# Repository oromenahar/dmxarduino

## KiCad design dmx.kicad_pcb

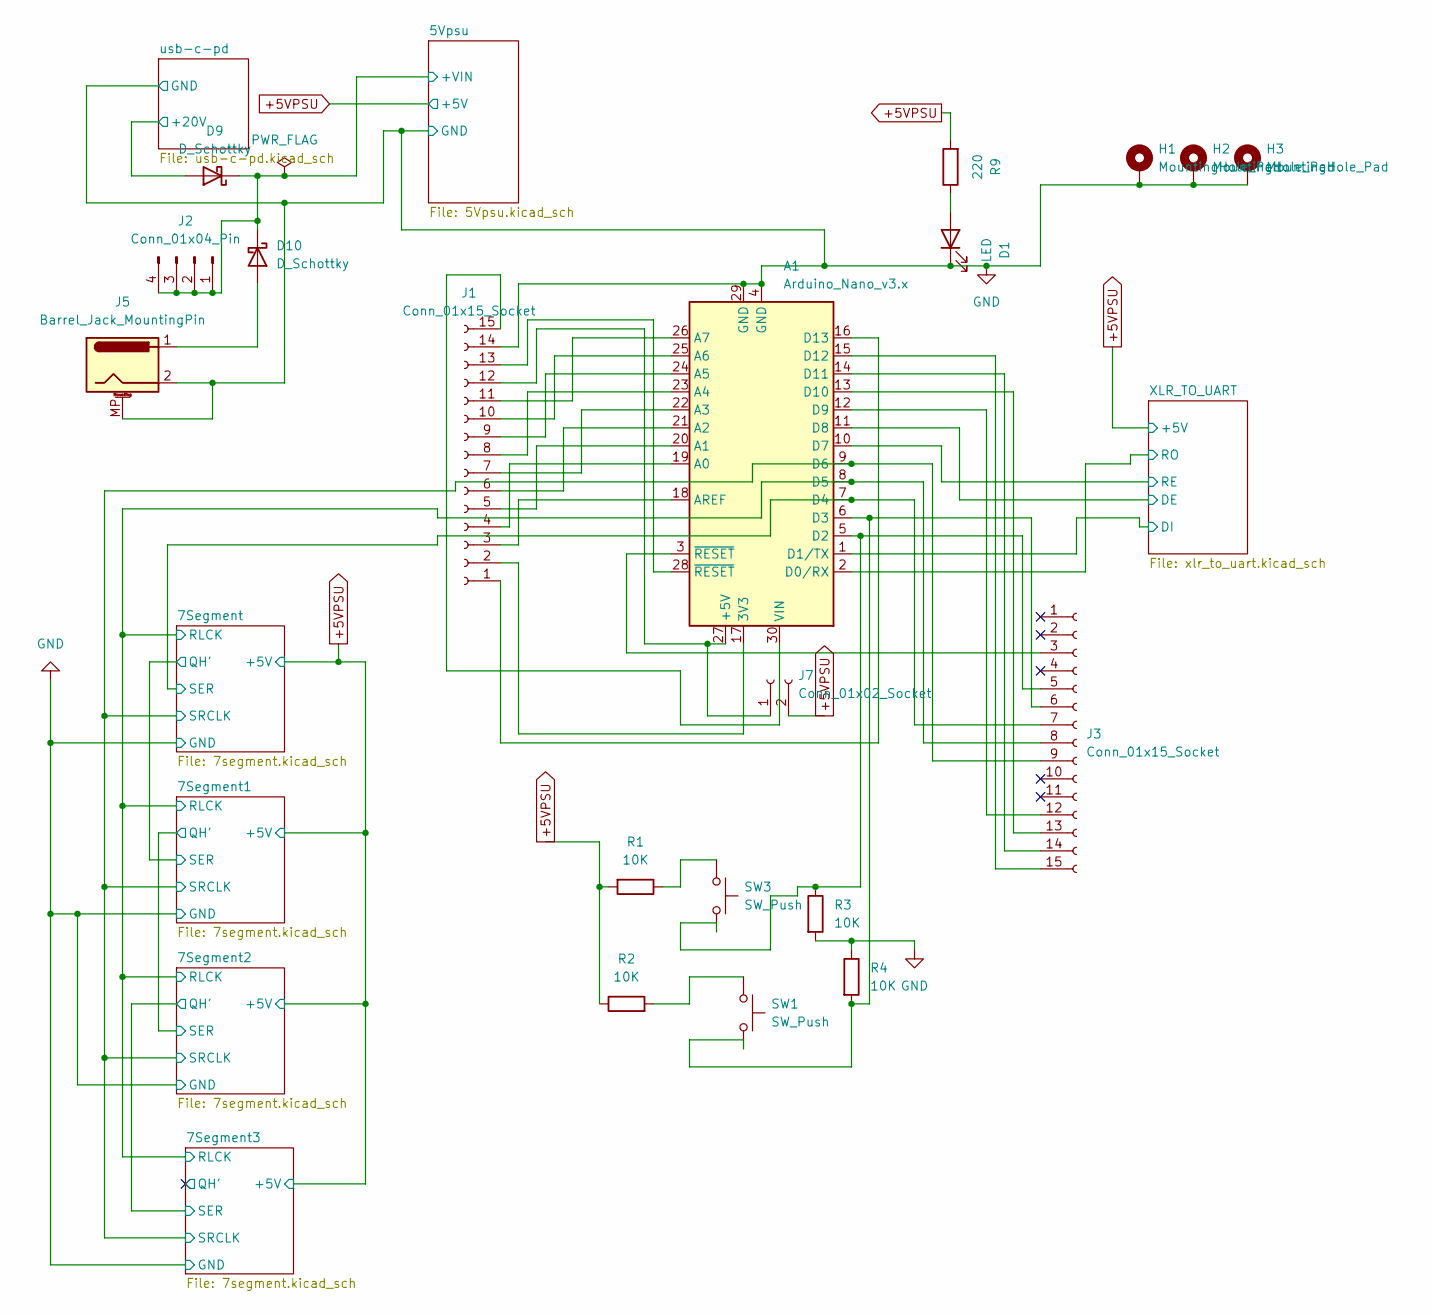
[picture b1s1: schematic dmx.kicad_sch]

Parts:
A1: Arduino_Nano_v3.x; Arduino_Nano_WithMountingHoles
D1: LED; LED_0603_1608Metric; LCSC C434420
D9, D10: D_Schottky; D_SMC; LCSC C2898934
H1, H2, H3: MountingHole_Pad; MountingHole_3.2mm_M3_DIN965_Pad
J1, J3: Conn_01x15_Socket; PinHeader_1x15_P2.54mm_Vertical
J2: Conn_01x04_Pin; PinHeader_1x04_P2.54mm_Vertical
J5: Barrel_Jack_MountingPin; BarrelJack_CLIFF_FC681465S_SMT_Horizontal; LCSC C2880543
J7: Conn_01x02_Socket; PinSocket_1x02_P2.54mm_Vertical
R1, R2, R3, R4: 10K; R_0603_1608Metric
R9: 220; R_0402_1005Metric; LCSC C25091
SW1, SW3: SW_Push; SW_PUSH_6mm

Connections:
+5VPSU: J7.2, R1.2, R2.1, R9.2; also elsewhere on the board
/5Vpsu/+VIN: D9.1 (K), D10.1 (K), J2.1, J2.2, J2.3, J2.4; also elsewhere on the board
/7Segment/RLCK: A1.8 (D5), J3.8; also elsewhere on the board
/7Segment/SER: A1.7 (D4), J3.7; also elsewhere on the board
/7Segment/SRCLK: A1.9 (D6), J3.9; also elsewhere on the board
/XLR_TO_UART/DE: A1.11 (D8); also elsewhere on the board
/XLR_TO_UART/DI: A1.1 (D1/TX); also elsewhere on the board
/XLR_TO_UART/RE: A1.10 (D7); also elsewhere on the board
/XLR_TO_UART/RO: A1.2 (D0/RX); also elsewhere on the board
/usb-c-pd/+20V: D9.2 (A); also elsewhere on the board
GND: A1.4 (GND), A1.29 (GND), D1.1 (K), H1.1, H2.1, H3.1, J1.14, J5.2, J5.MP (MountPin), R3.2, R4.1; also elsewhere on the board
unnamed: A1.17 (3V3), J1.2
unnamed: A1.27 (+5V), J1.12, J7.1
unnamed: A1.19 (A0), J1.4
unnamed: A1.20 (A1), J1.5
unnamed: A1.21 (A2), J1.6
unnamed: A1.22 (A3), J1.7
unnamed: A1.23 (A4), J1.8
unnamed: A1.24 (A5), J1.9
unnamed: A1.25 (A6), J1.10
unnamed: A1.26 (A7), J1.11
unnamed: A1.18 (AREF), J1.3
unnamed: A1.5 (D2), J3.5, R3.1, SW3.2
unnamed: A1.6 (D3), J3.6, R4.2, SW1.2
unnamed: A1.12 (D9), J3.12
unnamed: A1.13 (D10), J3.13
unnamed: A1.14 (D11), J3.14
unnamed: A1.15 (D12), J3.15
unnamed: A1.16 (D13), J1.1
unnamed: A1.30 (VIN), J1.15
unnamed: D1.2 (A), R9.1
unnamed: D10.2 (A), J5.1
unnamed: A1.28 (~RESET), J1.13
unnamed: A1.3 (~RESET), J3.3
unnamed: R1.1, SW3.1
unnamed: R2.2, SW1.1

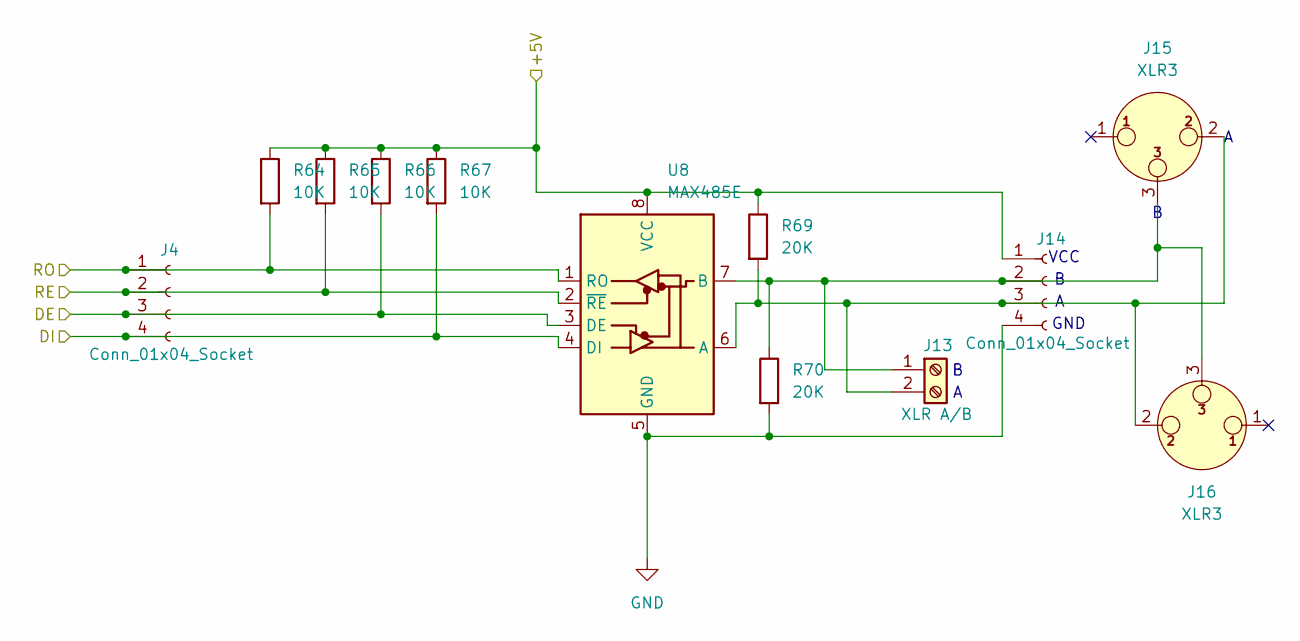
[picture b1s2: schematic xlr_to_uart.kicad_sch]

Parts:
J4, J14: Conn_01x04_Socket; PinHeader_1x04_P2.54mm_Vertical
J13: XLR A/B; TerminalBlock_bornier-2_P5.08mm
J15, J16: XLR3; Jack_XLR_Neutrik_NC3FAAH-0_Horizontal
R64, R65, R66, R67: 10K; R_0603_1608Metric
R69, R70: 20K; R_0402_1005Metric
U8: MAX485E; SOP-8_3.9x4.9mm_P1.27mm; LCSC C5279041

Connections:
+5VPSU: J14.1, R64.1, R65.1, R66.1, R67.1, R69.1, U8.8 (VCC); also elsewhere on the board
/XLR_TO_UART/DE: J4.3, R66.2, U8.3 (DE); also elsewhere on the board
/XLR_TO_UART/DI: J4.4, R67.2, U8.4 (DI); also elsewhere on the board
/XLR_TO_UART/RE: J4.2, R65.2, U8.2 (~RE); also elsewhere on the board
/XLR_TO_UART/RO: J4.1, R64.2, U8.1 (RO); also elsewhere on the board
GND: J14.4, R70.2, U8.5 (GND); also elsewhere on the board
unnamed: J13.1, J14.2, J15.3, J16.3, R70.1, U8.7 (B)
unnamed: J13.2, J14.3, J15.2, J16.2, R69.2, U8.6 (A)

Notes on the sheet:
VCC
GND

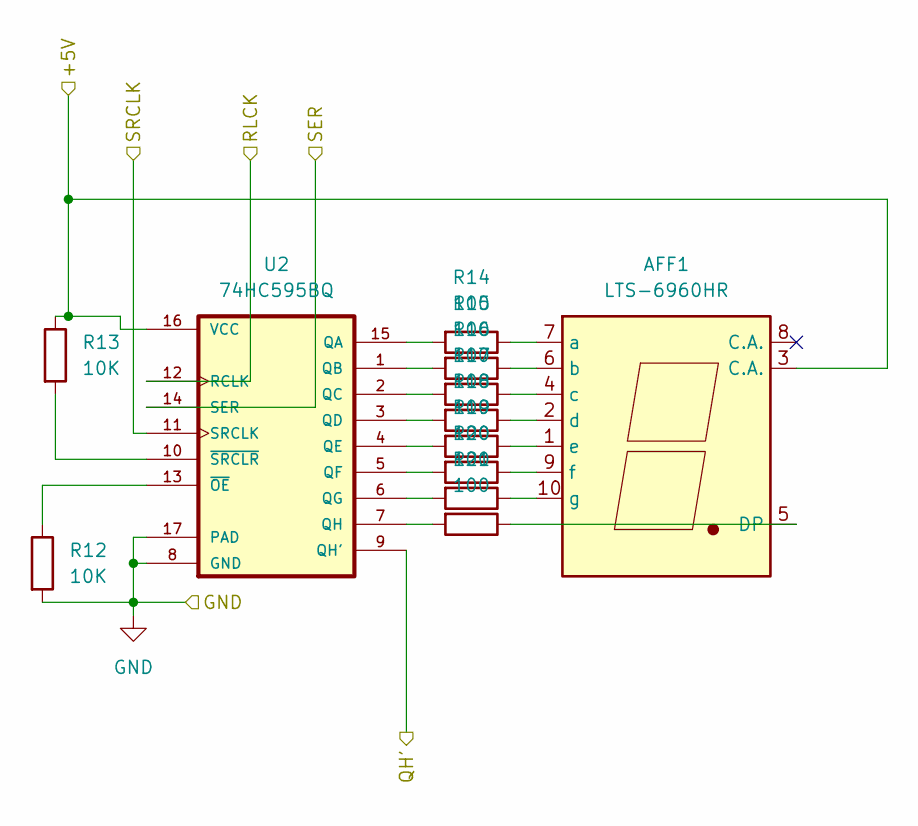
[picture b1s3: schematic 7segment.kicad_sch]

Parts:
AFF1: LTS-6960HR; 7SegmentLED_LTS6760_LTS6780
R12, R13: 10K; R_0603_1608Metric
R14, R15, R16, R17, R18, R19, R20, R21: 100; R_0603_1608Metric; LCSC C22775
U2: 74HC595BQ; DHVQFN-16-1EP_2.5x3.5mm_P0.5mm_EP1x2mm; LCSC C730243

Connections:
+5VPSU: AFF1.3 (C.A.), R13.1, U2.16 (VCC); also elsewhere on the board
/7Segment/QH': U2.9 (QH'); also elsewhere on the board
/7Segment/RLCK: U2.12 (RCLK); also elsewhere on the board
/7Segment/SER: U2.14 (SER); also elsewhere on the board
/7Segment/SRCLK: U2.11 (SRCLK); also elsewhere on the board
GND: R12.2, U2.8 (GND), U2.17 (PAD); also elsewhere on the board
unnamed: AFF1.5 (DP), R21.1
unnamed: AFF1.7 (a), R14.1
unnamed: AFF1.6 (b), R15.1
unnamed: AFF1.4 (c), R16.1
unnamed: AFF1.2 (d), R17.1
unnamed: AFF1.1 (e), R18.1
unnamed: AFF1.9 (f), R19.1
unnamed: AFF1.10 (g), R20.1
unnamed: R14.2, U2.15 (QA)
unnamed: R15.2, U2.1 (QB)
unnamed: R16.2, U2.2 (QC)
unnamed: R17.2, U2.3 (QD)
unnamed: R18.2, U2.4 (QE)
unnamed: R19.2, U2.5 (QF)
unnamed: R20.2, U2.6 (QG)
unnamed: R21.2, U2.7 (QH)
unnamed: R12.1, U2.13 (~OE)
unnamed: R13.2, U2.10 (~SRCLR)

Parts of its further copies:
AFF2, AFF3, AFF4: LTS-6960HR; 7SegmentLED_LTS6760_LTS6780
R22, R23, R41, R42, R51, R52: 10K; R_0603_1608Metric
R24, R25, R26, R27, R28, R29, R30, R40, R43, R44, R45, R46, R47, R48, R49, R50, R53, R54, R55, R56, R57, R58, R59, R60: 100; R_0603_1608Metric; LCSC C22775
U3, U4, U5: 74HC595BQ; DHVQFN-16-1EP_2.5x3.5mm_P0.5mm_EP1x2mm; LCSC C730243

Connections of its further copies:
+5VPSU: AFF2.3 (C.A.), AFF3.3 (C.A.), AFF4.3 (C.A.), R23.1, R42.1, R52.1, U3.16 (VCC), U4.16 (VCC), U5.16 (VCC); also elsewhere on the board
/7Segment1/QH': U3.9 (QH'), U4.14 (SER)
/7Segment2/QH': U4.9 (QH'), U5.14 (SER)
/7Segment3/QH': U5.9 (QH')
/7Segment/QH': U3.14 (SER); also elsewhere on the board
/7Segment/RLCK: U3.12 (RCLK), U4.12 (RCLK), U5.12 (RCLK); also elsewhere on the board
/7Segment/SRCLK: U3.11 (SRCLK), U4.11 (SRCLK), U5.11 (SRCLK); also elsewhere on the board
GND: R22.2, R41.2, R51.2, U3.8 (GND), U3.17 (PAD), U4.8 (GND), U4.17 (PAD), U5.8 (GND), U5.17 (PAD); also elsewhere on the board
unnamed: AFF2.5 (DP), R40.1
unnamed: AFF2.7 (a), R24.1
unnamed: AFF2.6 (b), R25.1
unnamed: AFF2.4 (c), R26.1
unnamed: AFF2.2 (d), R27.1
unnamed: AFF2.1 (e), R28.1
unnamed: AFF2.9 (f), R29.1
unnamed: AFF2.10 (g), R30.1
unnamed: AFF3.5 (DP), R50.1
unnamed: AFF3.7 (a), R43.1
unnamed: AFF3.6 (b), R44.1
unnamed: AFF3.4 (c), R45.1
unnamed: AFF3.2 (d), R46.1
unnamed: AFF3.1 (e), R47.1
unnamed: AFF3.9 (f), R48.1
unnamed: AFF3.10 (g), R49.1
unnamed: AFF4.5 (DP), R60.1
unnamed: AFF4.7 (a), R53.1
unnamed: AFF4.6 (b), R54.1
unnamed: AFF4.4 (c), R55.1
unnamed: AFF4.2 (d), R56.1
unnamed: AFF4.1 (e), R57.1
unnamed: AFF4.9 (f), R58.1
unnamed: AFF4.10 (g), R59.1
unnamed: R24.2, U3.15 (QA)
unnamed: R25.2, U3.1 (QB)
unnamed: R26.2, U3.2 (QC)
unnamed: R27.2, U3.3 (QD)
unnamed: R28.2, U3.4 (QE)
unnamed: R29.2, U3.5 (QF)
unnamed: R30.2, U3.6 (QG)
unnamed: R40.2, U3.7 (QH)
unnamed: R22.1, U3.13 (~OE)
unnamed: R23.2, U3.10 (~SRCLR)
unnamed: R43.2, U4.15 (QA)
unnamed: R44.2, U4.1 (QB)
unnamed: R45.2, U4.2 (QC)
unnamed: R46.2, U4.3 (QD)
unnamed: R47.2, U4.4 (QE)
unnamed: R48.2, U4.5 (QF)
unnamed: R49.2, U4.6 (QG)
unnamed: R50.2, U4.7 (QH)
unnamed: R41.1, U4.13 (~OE)
unnamed: R42.2, U4.10 (~SRCLR)
unnamed: R53.2, U5.15 (QA)
unnamed: R54.2, U5.1 (QB)
unnamed: R55.2, U5.2 (QC)
unnamed: R56.2, U5.3 (QD)
unnamed: R57.2, U5.4 (QE)
unnamed: R58.2, U5.5 (QF)
unnamed: R59.2, U5.6 (QG)
unnamed: R60.2, U5.7 (QH)
unnamed: R51.1, U5.13 (~OE)
unnamed: R52.2, U5.10 (~SRCLR)

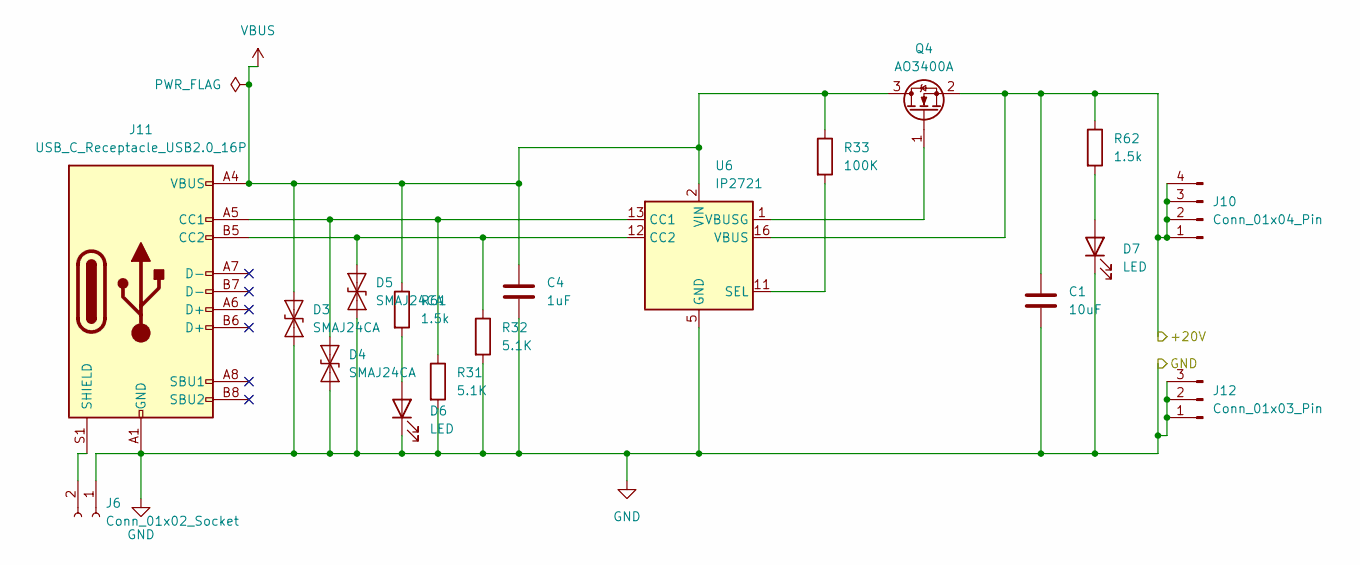
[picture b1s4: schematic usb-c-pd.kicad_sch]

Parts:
C1: 10uF; C_0603_1608Metric
C4: 1uF; C_0603_1608Metric
D3, D4, D5: SMAJ24CA; D_SMA; LCSC C19077537
D6, D7: LED; LED_0603_1608Metric; LCSC C497935
J6: Conn_01x02_Socket; PinSocket_1x02_P2.54mm_Vertical
J10: Conn_01x04_Pin; PinHeader_1x04_P2.54mm_Vertical
J11: USB_C_Receptacle_USB2.0_16P; TYPE-C-31-M-12; LCSC C165948
J12: Conn_01x03_Pin; PinHeader_1x03_P2.54mm_Vertical
Q4: AO3400A; SOT-23; LCSC C20917
R31, R32: 5.1K; R_0603_1608Metric
R33: 100K; R_0603_1608Metric
R61, R62: 1.5k; R_2010_5025Metric
U6: IP2721; TSSOP-16_4.4x5mm_P0.65mm; LCSC C603176

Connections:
/usb-c-pd/+20V: C1.1, J10.1, J10.2, J10.3, J10.4, Q4.2 (S), R62.1, U6.16 (VBUS); also elsewhere on the board
GND: C1.2, C4.2, D3.1 (A1), D4.1 (A1), D5.1 (A1), D6.1 (K), D7.1 (K), J6.1, J11.A1 (GND), J11.A12 (GND), J11.B1 (GND), J11.B12 (GND), J12.1, J12.2, J12.3, R31.2, R32.2, U6.5 (GND); also elsewhere on the board
unnamed: D4.2 (A2), J11.A5 (CC1), R31.1, U6.13 (CC1)
unnamed: D5.2 (A2), J11.B5 (CC2), R32.1, U6.12 (CC2)
unnamed: D6.2 (A), R61.2
unnamed: D7.2 (A), R62.2
unnamed: J6.2, J11.S1 (SHIELD)
unnamed: Q4.1 (G), U6.1 (VBUSG)
unnamed: R33.2, U6.11 (SEL)
VBUS: C4.1, D3.2 (A2), J11.A4 (VBUS), J11.A9 (VBUS), J11.B4 (VBUS), J11.B9 (VBUS), Q4.3 (D), R33.1, R61.1, U6.2 (VIN)

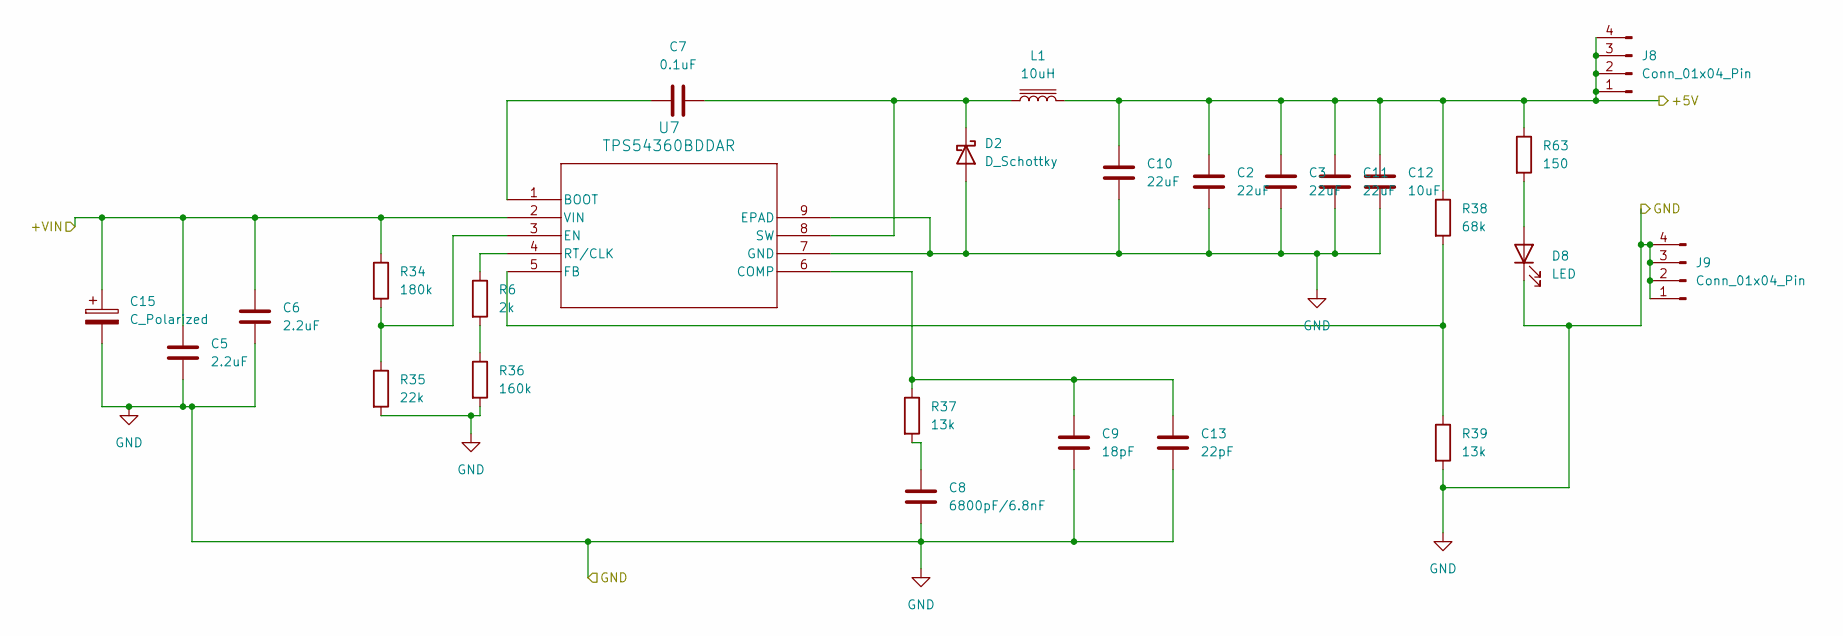
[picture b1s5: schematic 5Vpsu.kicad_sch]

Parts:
C2, C3, C10, C11: 22uF; C_0805_2012Metric; LCSC C45783
C5, C6: 2.2uF; C_1206_3216Metric_Pad1.33x1.80mm_HandSolder; LCSC C1021612
C7: 0.1uF; C_0603_1608Metric
C8: 6800pF/6.8nF; C_0603_1608Metric; LCSC C1631
C9: 18pF; C_0603_1608Metric; LCSC C1653
C12: 10uF; C_0805_2012Metric; LCSC C15850
C13: 22pF; C_0603_1608Metric; LCSC C1647
C15: C_Polarized; CP_Radial_D5.0mm_P2.50mm
D2: D_Schottky; D_SMC; LCSC C2898934
D8: LED; LED_0603_1608Metric; LCSC C497935
J8, J9: Conn_01x04_Pin; PinHeader_1x04_P2.54mm_Vertical
L1: 10uH; L_7.3x7.3_H3.5; LCSC C2961335
R6: 2k; R_0603_1608Metric; LCSC C22975
R34: 180k; R_0603_1608Metric
R35: 22k; R_0603_1608Metric
R36: 160k; R_0603_1608Metric; LCSC C22813
R37: 13k; R_0603_1608Metric
R38: 68k; R_0603_1608Metric; LCSC C23231
R39: 13k; R_0603_1608Metric; LCSC C22797
R63: 150; R_0603_1608Metric; LCSC C8218
U7: TPS54360BDDAR; SOIC-8-1EP_3.9x4.9mm_P1.27mm_EP2.29x3mm; LCSC C524806

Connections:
+5VPSU: C2.2, C3.2, C10.2, C11.2, C12.2, J8.1, J8.2, J8.3, J8.4, L1.1, R38.1, R63.1; also elsewhere on the board
/5Vpsu/+VIN: C5.1, C6.1, C15.1, R34.1, U7.2 (VIN); also elsewhere on the board
GND: C2.1, C3.1, C5.2, C6.2, C8.1, C9.1, C10.1, C11.1, C12.1, C13.1, C15.2, D2.2 (A), D8.1 (K), J9.1, J9.2, J9.3, J9.4, R35.2, R36.2, R39.2, U7.7 (GND), U7.9 (EPAD); also elsewhere on the board
unnamed: C8.2, R37.2
unnamed: C7.2, D2.1 (K), L1.2, U7.8 (SW)
unnamed: D8.2 (A), R63.2
unnamed: R6.2, R36.1
unnamed: C7.1, U7.1 (BOOT)
unnamed: C9.2, C13.2, R37.1, U7.6 (COMP)
unnamed: R34.2, R35.1, U7.3 (EN)
unnamed: R38.2, R39.1, U7.5 (FB)
unnamed: R6.1, U7.4 (RT/CLK)

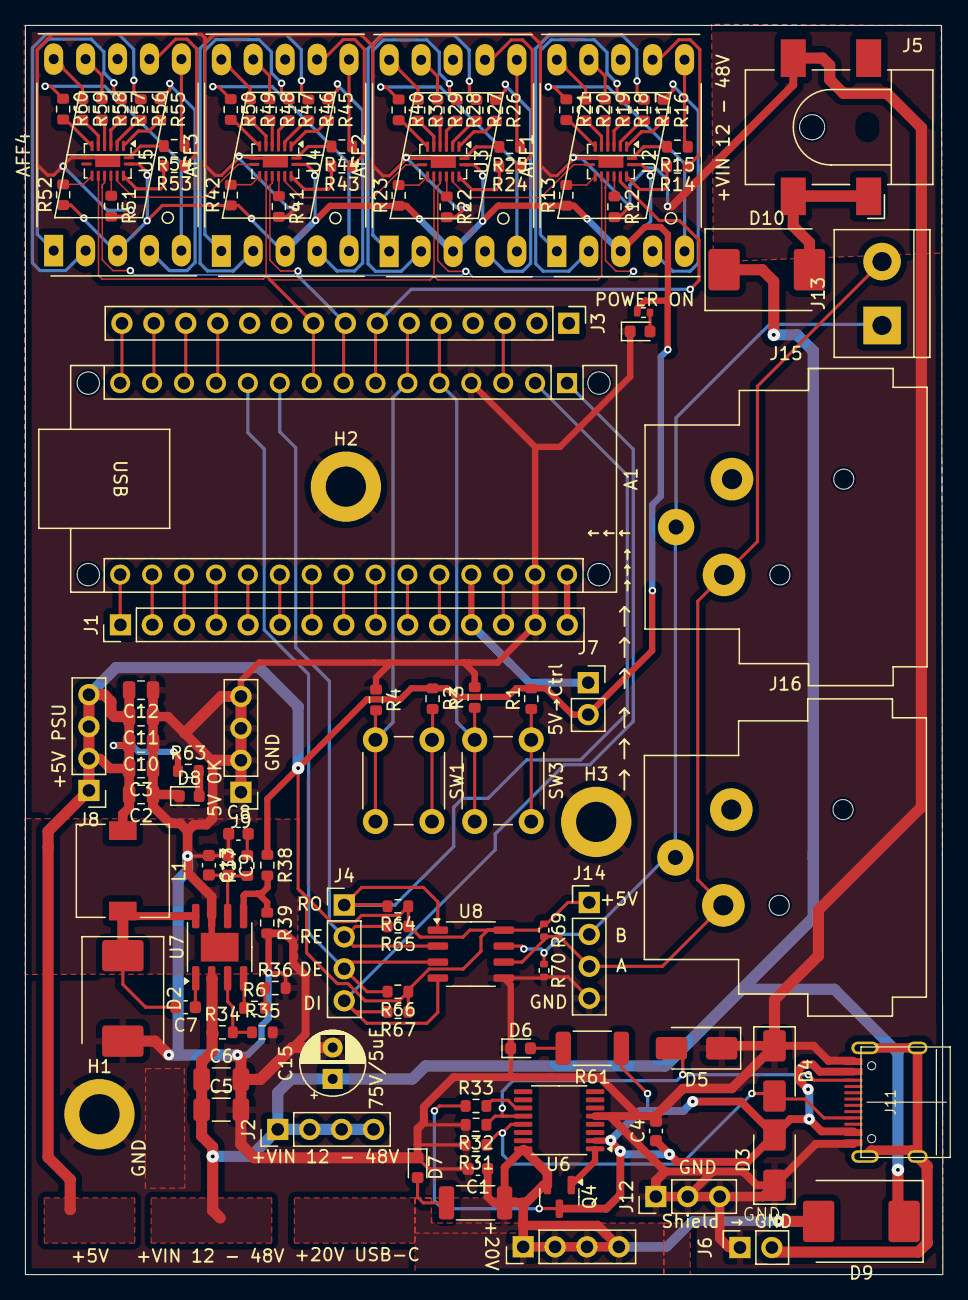
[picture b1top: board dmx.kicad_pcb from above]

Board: 2 copper layers, 73.0 x 99.4 mm, 123 parts (0 on the bottom side), 130 nets.

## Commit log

2024-05-28 init dmx to arduino
2024-05-28 switch to cheaper components.
2024-05-30 replace extended components with basic components.
2024-05-30 add a +5V bridge to disbale the arduino
2024-05-31 change some last parts.
